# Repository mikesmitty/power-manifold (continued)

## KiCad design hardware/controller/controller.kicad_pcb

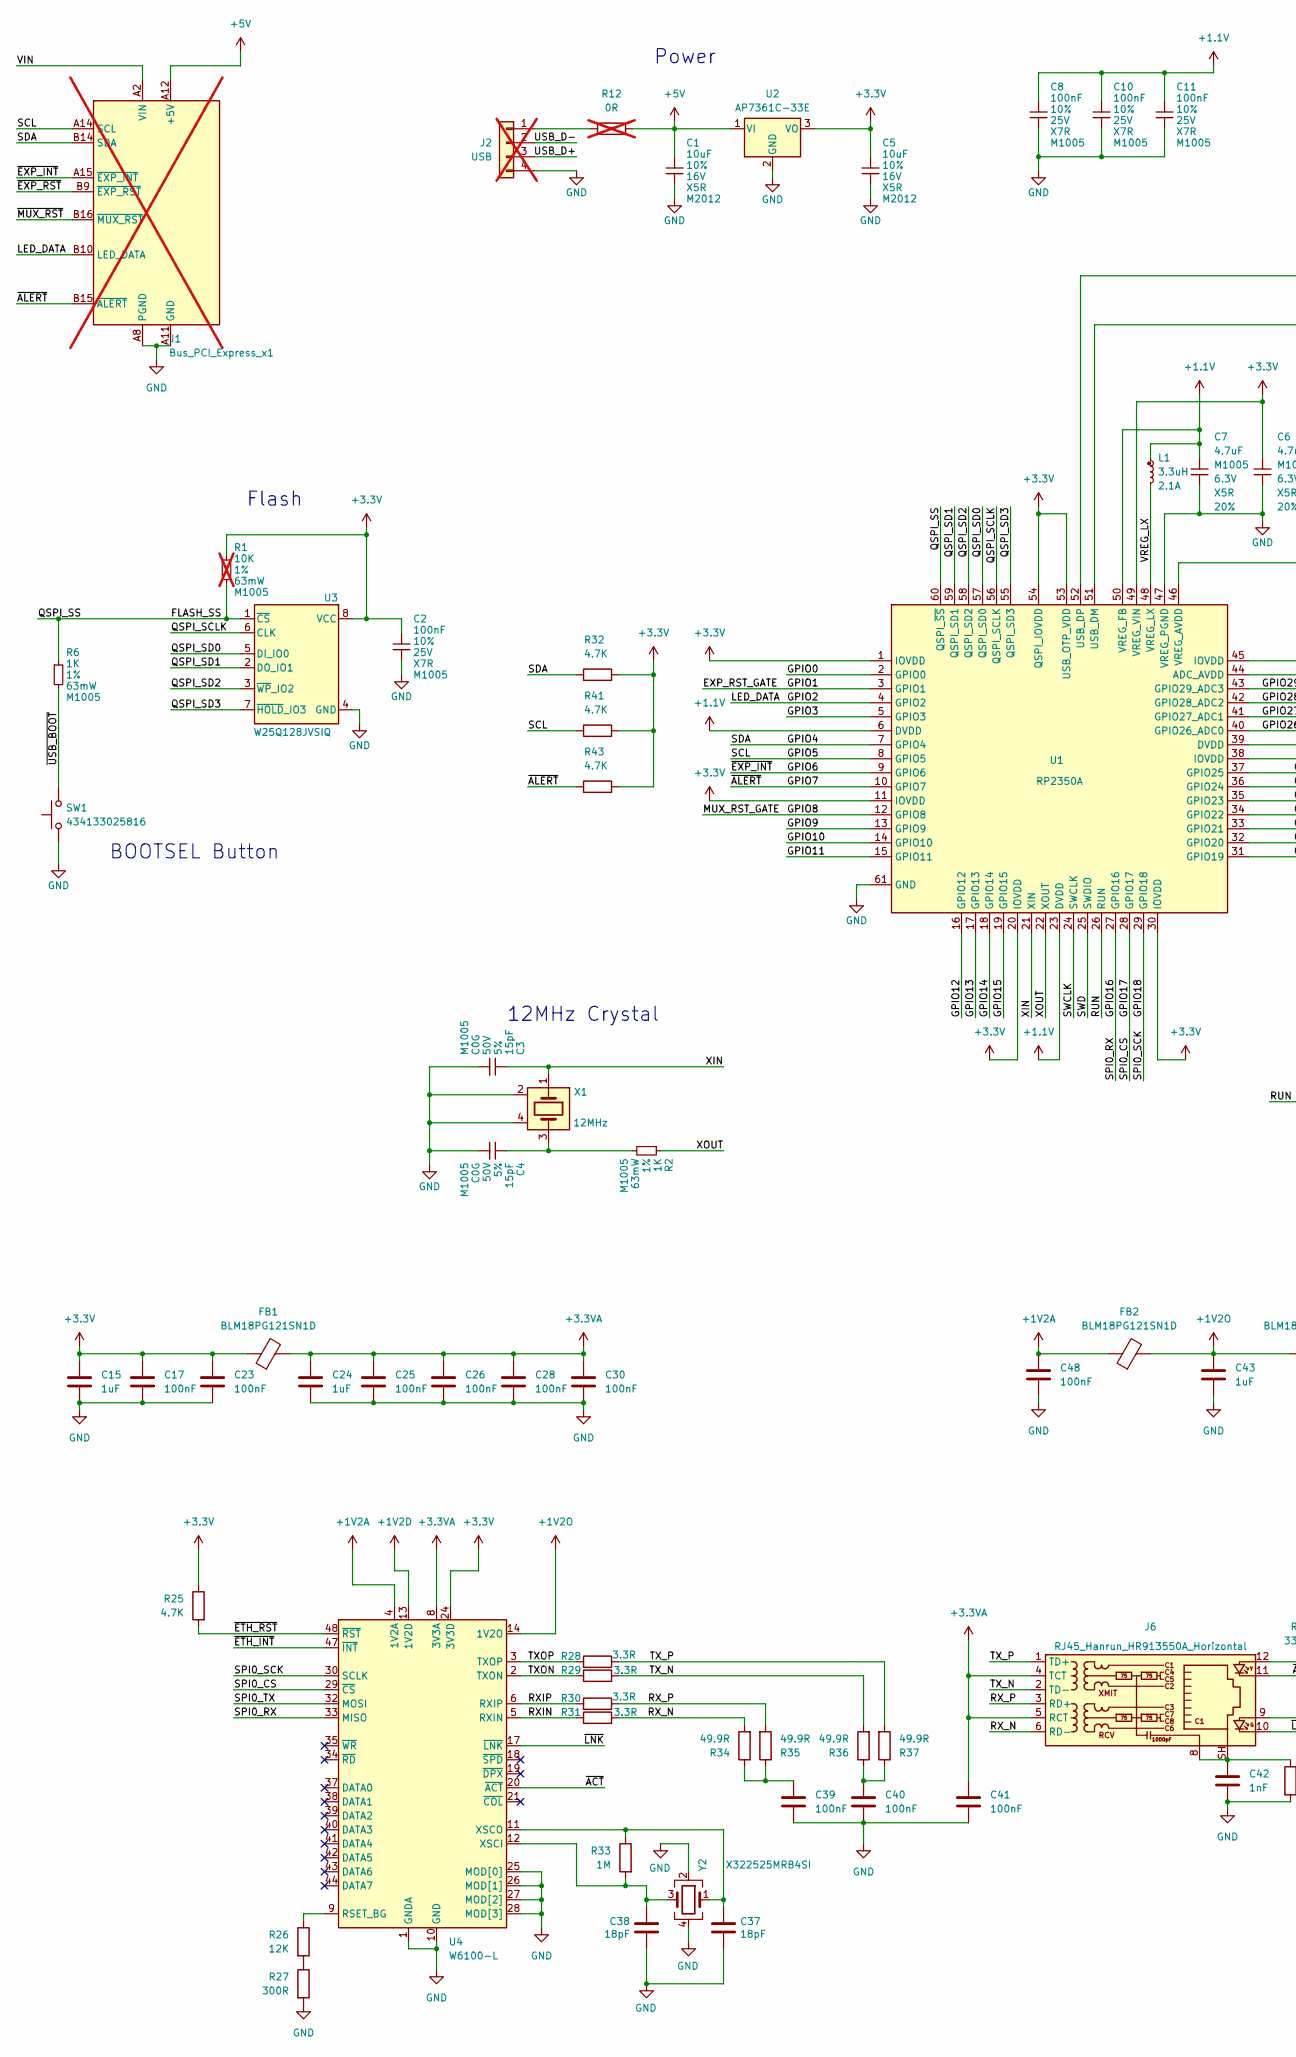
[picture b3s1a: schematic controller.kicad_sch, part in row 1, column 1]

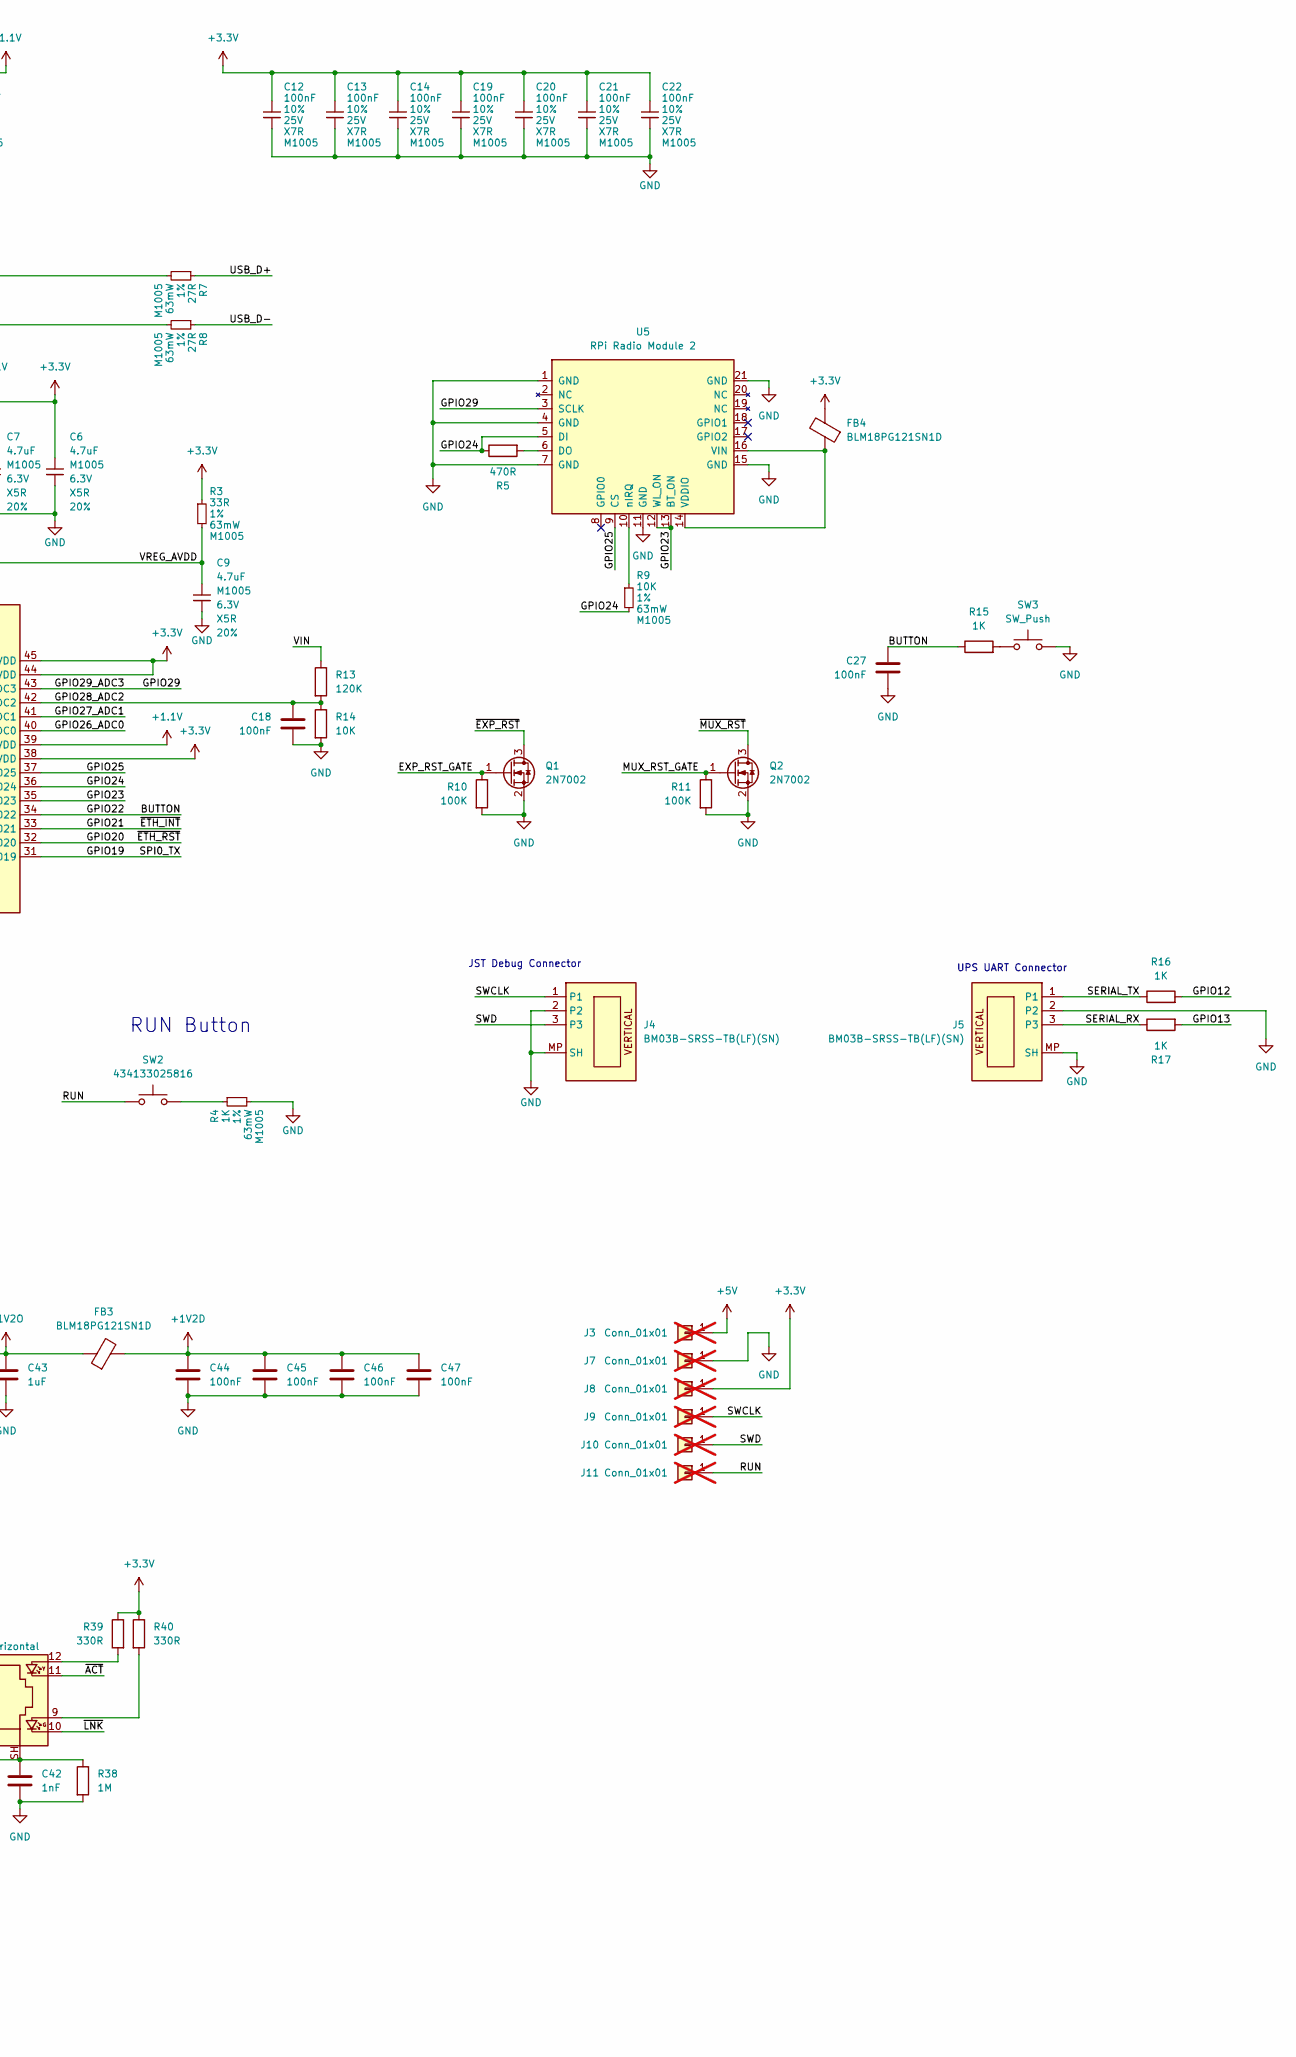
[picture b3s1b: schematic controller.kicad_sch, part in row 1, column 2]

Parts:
C1, C5: 10uF; C_0805_2012Metric; voltage 16V; tolerance 10%; part_uid RP-01GYSK-AVBE41; LCSC C1713
C2, C8, C10, C11, C12, C13, C14, C19, C20, C21, C22: 100nF; C_0402_1005Metric; voltage 25V; tolerance 10%; part_uid RP-01BJ9Y-KRGF41; LCSC C307331
C3, C4: 15pF; C_0402_1005Metric; voltage 50V; tolerance 5%; part_uid RP-01C89W-LLY9XV; LCSC C1548
C6, C7: 4.7uF; C_0402_Wide; voltage 6.3V; tolerance 20%; part_uid RP-019A1P-0C2GHY; LCSC C23733
C9: 4.7uF; C_0402_1005Metric; voltage 6.3V; tolerance 20%; part_uid RP-019A1P-0C2GHY; LCSC C23733
C15, C24, C43: 1uF; C_0402_1005Metric; LCSC C52923
C17, C18, C23, C25, C26, C27, C28, C30, C39, C40, C41, C44, C45, C46, C47, C48: 100nF; C_0402_1005Metric; LCSC C307331
C37, C38: 18pF; C_0402_1005Metric; LCSC C1549
C42: 1nF; C_1206_3216Metric; LCSC C9196
FB1, FB2, FB3, FB4: BLM18PG121SN1D; L_0603_1608Metric; LCSC C14709
J1: Bus_PCI_Express_x1; BUS_PCIexpress_x1; not fitted
J2: USB; PinHeader_1x04_P2.54mm_Vertical; not fitted
J3, J7, J8, J9, J10, J11: Conn_01x01; TestPoint_Pad_D1.5mm; not fitted
J4, J5: BM03B-SRSS-TB(LF)(SN); JST_SH_BM03B-SRSS-TB_1x03-1MP_P1.00mm_Vertical; manufacturer_pn BM03B-SRSS-TB(LF)(SN); LCSC C160389
J6: RJ45_Hanrun_HR913550A_Horizontal; RJ45_Hanrun_HR911105A_Horizontal; LCSC C163507
L1: 3.3uH; L_pol_2016; tolerance 20%; part_uid RP-01GY5D-2VC7WP; LCSC C42411119
Q1, Q2: 2N7002; SOT-23; LCSC C8545
R1: 10K; R_0402_1005Metric; tolerance 1%; voltage 50V; part_uid RP-019A1P-53DHSX; not fitted
R2, R4, R6: 1K; R_0402_1005Metric; tolerance 1%; voltage 50V; part_uid RP-019A1P-4Z6ZWY; LCSC C11702
R3: 33R; R_0402_1005Metric; tolerance 1%; voltage 50V; part_uid RP-019A1P-58PW9L; LCSC C25105
R5: 470R; R_0402_1005Metric; LCSC C25117
R7, R8: 27R; R_0402_1005Metric; tolerance 1%; voltage 50V; part_uid RP-01C89V-LTEYC4; LCSC C25100
R9: 10K; R_0402_1005Metric; tolerance 1%; voltage 50V; part_uid RP-019A1P-53DHSX; LCSC C25744
R10, R11: 100K; R_0402_1005Metric; LCSC C25741
R12: 0R; R_0603_1608Metric; not fitted
R13: 120K; R_0603_1608Metric; LCSC C25808
R14: 10K; R_0402_1005Metric; LCSC C25744
R15, R16, R17: 1K; R_0402_1005Metric; LCSC C11702
R25, R32, R41, R43: 4.7K; R_0402_1005Metric; LCSC C25900
R26: 12K; R_0402_1005Metric; Tolerance 1%; LCSC C25752
R27: 300R; R_0402_1005Metric; LCSC C25102
R28, R29, R30, R31: 3.3R; R_0402_1005Metric; LCSC C2933094
R33: 1M; R_0402_1005Metric; LCSC C26083
R34, R35, R36, R37: 49.9R; R_0402_1005Metric; LCSC C25120
R38: 1M; R_1206_3216Metric; LCSC C17927
R39, R40: 330R; R_0402_1005Metric; LCSC C25104
SW1, SW2: 434133025816; SW_Push_1P1T_NO_Vertical_Wuerth_434133025816; part_uid RP-01H0MT-6E9H8F; LCSC C5504987
SW3: SW_Push; SW_SPST_B3U-3000P; LCSC C963349
U1: RP2350A; QFN-60-1EP_7x7mm_P0.4mm_EP3.4x3.4mm_ThermalVias; part_uid RP-01HA9H-9K5E8T; LCSC C42411118
U2: AP7361C-33E; SOT-223-3_TabPin2; LCSC C500795
U3: W25Q128JVSIQ; SOIC-8_5.3x5.3mm_P1.27mm; voltage 2.7-3.6V; part_uid RP-01JWD4-F1H4N9; LCSC C97521
U4: W6100-L; LQFP-48_7x7mm_P0.5mm; LCSC C911393
U5: RPi Radio Module 2; RMC20452T; LCSC C49451547
X1: 12MHz; Crystal_SMD_Abracon_ABM8AIG-4Pin_3.2x2.5mm; tolerance 30ppm; part_uid RP-01G8X7-GS352B; LCSC C20625731
Y2: X322525MRB4SI; Crystal_SMD_3225-4Pin_3.2x2.5mm; LCSC C70593

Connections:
+1.1V: C7.1, C8.1, C10.1, C11.1, L1.1, U1.6 (DVDD), U1.23 (DVDD), U1.39 (DVDD), U1.50 (VREG_FB)
+1V2A: C48.1, FB2.1, U4.4 (1V2A)
+1V2D: C44.1, C45.1, C46.1, C47.1, FB3.2, U4.13 (1V2D), U4.22 (1V2D), U4.31 (1V2D), U4.45 (1V2D)
+1V2O: C43.1, FB2.2, FB3.1, U4.14 (1V2O)
+3.3V: C2.1, C5.1, C6.1, C12.1, C13.1, C14.1, C15.1, C17.1, C19.1, C20.1, C21.1, C22.1, C23.1, FB1.1, FB4.2, J8.1 (Pin_1_1), R1.1, R3.1, R25.1, R32.2, R39.1, R40.1, R41.2, R43.2, U1.1 (IOVDD), U1.11 (IOVDD), U1.20 (IOVDD), U1.30 (IOVDD), U1.38 (IOVDD), U1.44 (ADC_AVDD), U1.45 (IOVDD), U1.49 (VREG_VIN), U1.53 (USB_OTP_VDD), U1.54 (QSPI_IOVDD), U2.3 (VO), U3.8 (VCC), U4.24 (3V3D), U4.36 (3V3D)
+3.3VA: C24.1, C25.1, C26.1, C28.1, C30.1, C41.1, FB1.2, J6.4 (TCT), J6.5 (RCT), U4.8 (3V3A), U4.15 (3V3A)
+5V: C1.1, J1.A12 (+5V), J1.B12 (+5V), J3.1 (Pin_1_1), R12.2, U2.1 (VI)
/BUTTON: C27.1, R15.1, U1.34 (GPIO22)
/EXP_RST_GATE: Q1.1 (G), R10.1, U1.3 (GPIO1)
/FLASH_SS: R1.2, R6.1, U1.60 (QSPI_~SS), U3.1 (~CS)
/GPIO0: U1.2 (GPIO0)
/GPIO2: J1.B10 (LED_DATA), U1.4 (GPIO2)
/GPIO3: U1.5 (GPIO3)
/GPIO4: J1.B14 (SDA), R32.1, U1.7 (GPIO4)
/GPIO5: J1.A14 (SCL), R41.1, U1.8 (GPIO5)
/GPIO6: J1.A15 (~EXP_INT), U1.9 (GPIO6)
/GPIO7: J1.B15 (~ALERT), R43.1, U1.10 (GPIO7)
/GPIO8: Q2.1 (G), R11.1, U1.12 (GPIO8)
/GPIO9: U1.13 (GPIO9)
/GPIO10: U1.14 (GPIO10)
/GPIO11: U1.15 (GPIO11)
/GPIO12: R16.2, U1.16 (GPIO12)
/GPIO13: R17.2, U1.17 (GPIO13)
/GPIO14: U1.18 (GPIO14)
/GPIO15: U1.19 (GPIO15)
/GPIO16: U1.27 (GPIO16), U4.33 (MISO)
/GPIO17: U1.28 (GPIO17), U4.29 (~CS)
/GPIO18: U1.29 (GPIO18), U4.30 (SCLK)
/GPIO19: U1.31 (GPIO19), U4.32 (MOSI)
/GPIO20: R25.2, U1.32 (GPIO20), U4.48 (~RST)
/GPIO21: U1.33 (GPIO21), U4.47 (~INT)
/GPIO23: U1.35 (GPIO23), U5.12 (WL_ON), U5.13 (BT_ON)
/GPIO24: R5.1, R9.2, U1.36 (GPIO24), U5.5 (DI)
/GPIO25: U1.37 (GPIO25), U5.9 (CS)
/GPIO26_ADC0: U1.40 (GPIO26_ADC0)
/GPIO27_ADC1: U1.41 (GPIO27_ADC1)
/GPIO28_ADC2: C18.1, R13.2, R14.1, U1.42 (GPIO28_ADC2)
/GPIO29: U1.43 (GPIO29_ADC3), U5.3 (SCLK)
/QSPI_SCLK: U1.56 (QSPI_SCLK), U3.6 (CLK)
/QSPI_SD0: U1.57 (QSPI_SD0), U3.5 (DI_IO0)
/QSPI_SD1: U1.59 (QSPI_SD1), U3.2 (DO_IO1)
/QSPI_SD2: U1.58 (QSPI_SD2), U3.3 (~WP_IO2)
/QSPI_SD3: U1.55 (QSPI_SD3), U3.7 (~HOLD_IO3)
/RUN: J11.1 (Pin_1_1), SW2.2, U1.26 (RUN)
/RXIN: R31.1, U4.5 (RXIN)
/RXIP: R30.1, U4.6 (RXIP)
/RX_N: J6.6 (RD-), R31.2, R34.2
/RX_P: J6.3 (RD+), R30.2, R35.2
/SERIAL_RX: J5.3, R17.1
/SERIAL_TX: J5.1, R16.1
/SWCLK: J4.1, J9.1 (Pin_1_1), U1.24 (SWCLK)
/SWD: J4.3, J10.1 (Pin_1_1), U1.25 (SWDIO)
/TXON: R29.1, U4.2 (TXON)
/TXOP: R28.1, U4.3 (TXOP)
/TX_N: J6.2 (TD-), R29.2, R36.2
/TX_P: J6.1 (TD+), R28.2, R37.2
/USB_D+: J2.3, R7.1
/USB_D-: J2.2, R8.1
/VIN: J1.A2 (VIN), J1.A3 (VIN), J1.A4 (VIN), J1.A5 (VIN), J1.A6 (VIN), J1.A7 (VIN), R13.1
/VREG_AVDD: C9.1, R3.2, U1.46 (VREG_AVDD)
/VREG_LX: L1.2, U1.48 (VREG_LX)
/XIN: C3.1, U1.21 (XIN), X1.1
/XOUT: R2.1, U1.22 (XOUT)
/~ACT: J6.11, U4.20 (~ACT)
/~EXP_RST: J1.B9 (~EXP_RST), Q1.3 (D)
/~LNK: J6.10, U4.17 (~LNK)
/~MUX_RST: J1.B16 (~MUX_RST), Q2.3 (D)
/~USB_BOOT: R6.2, SW1.2
GND: C1.2, C2.2, C3.2, C4.2, C5.2, C6.2, C7.2, C8.2, C9.2, C10.2, C11.2, C12.2, C13.2, C14.2, C15.2, C17.2, C18.2, C19.2, C20.2, C21.2, C22.2, C23.2, C24.2, C25.2, C26.2, C27.2, C28.2, C30.2, C37.2, C38.2, C39.2, C40.2, C41.2, C42.2, C43.2, C44.2, C45.2, C46.2, C47.2, C48.2, J1.A1 (GND), J1.A8 (PGND), J1.A9 (PGND), J1.A10 (PGND), J1.A11 (GND), J1.A13 (GND), J1.A16 (GND), J1.A17 (GND), J1.A18 (GND), J1.B1 (PGND), J1.B2 (PGND), J1.B3 (PGND), J1.B4 (PGND), J1.B5 (PGND), J1.B6 (PGND), J1.B7 (PGND), J1.B8 (PGND), J1.B11 (GND), J1.B13 (GND), J1.B17 (GND), J1.B18 (GND), J2.4, J4.2, J4.MP (SH), J5.2, J5.MP (SH), J7.1 (Pin_1_1), Q1.2 (S), Q2.2 (S), R4.2, R10.2, R11.2, R14.2, R27.2, R38.2, SW1.1, SW3.2, U1.47 (VREG_PGND), U1.61 (GND), U2.2 (GND), U3.4 (GND), U4.1 (GNDA), U4.7 (GNDA), U4.10 (GND), U4.16 (GNDA), U4.23 (GND), U4.25 (MOD[0]), U4.26 (MOD[1]), U4.27 (MOD[2]), U4.28 (MOD[3]), U4.46 (GND), U5.1 (GND), U5.4 (GND), U5.7 (GND), U5.11 (GND), U5.15 (GND), U5.21 (GND), X1.2, X1.4, Y2.2, Y2.4
unnamed: C4.1, R2.2, X1.3
unnamed: C39.1, R34.1, R35.1
unnamed: C40.1, R36.1, R37.1
unnamed: C42.1, J6.8, J6.SH, R38.1
unnamed: J2.1, R12.1
unnamed: J6.9, R40.2
unnamed: J6.12, R39.2
unnamed: R4.1, SW2.1
unnamed: R15.2, SW3.1
unnamed: R26.2, R27.1
unnamed: R8.2, U1.51 (USB_DM)
unnamed: R7.2, U1.52 (USB_DP)
unnamed: R26.1, U4.9 (RSET_BG)
unnamed: C38.1, R33.2, U4.12 (XSCI), Y2.3
unnamed: C37.1, R33.1, U4.11 (XSCO), Y2.1
unnamed: R5.2, U5.6 (DO)
unnamed: FB4.1, U5.14 (VDDIO), U5.16 (VIN)
unnamed: R9.1, U5.10 (nIRQ)

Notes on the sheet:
12MHz Crystal
RUN Button
Flash
BOOTSEL Button
JST Debug Connector
UPS UART Connector
Power

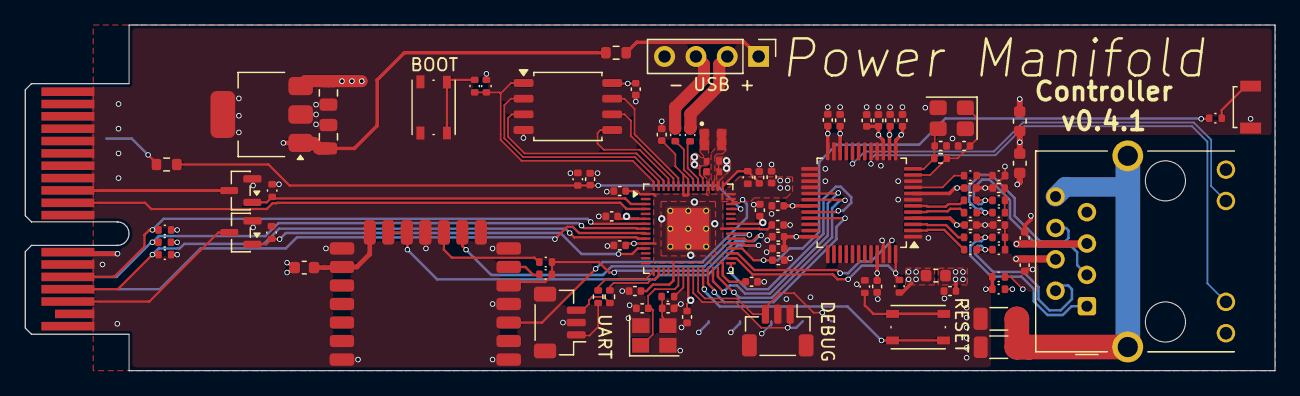
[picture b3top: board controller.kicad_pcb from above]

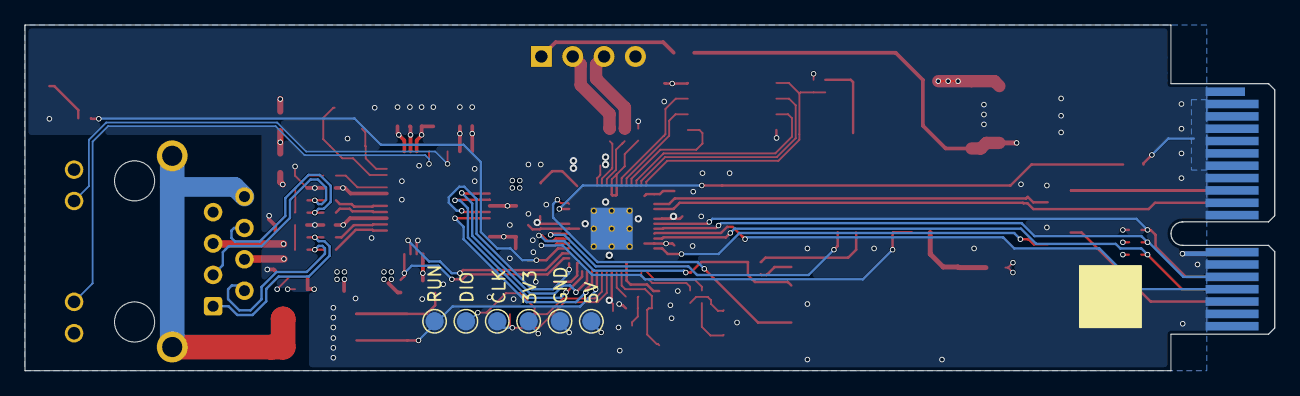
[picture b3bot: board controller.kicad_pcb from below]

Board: 4 copper layers, 101.2 x 28.0 mm, 103 parts (6 on the bottom side), 78 nets.

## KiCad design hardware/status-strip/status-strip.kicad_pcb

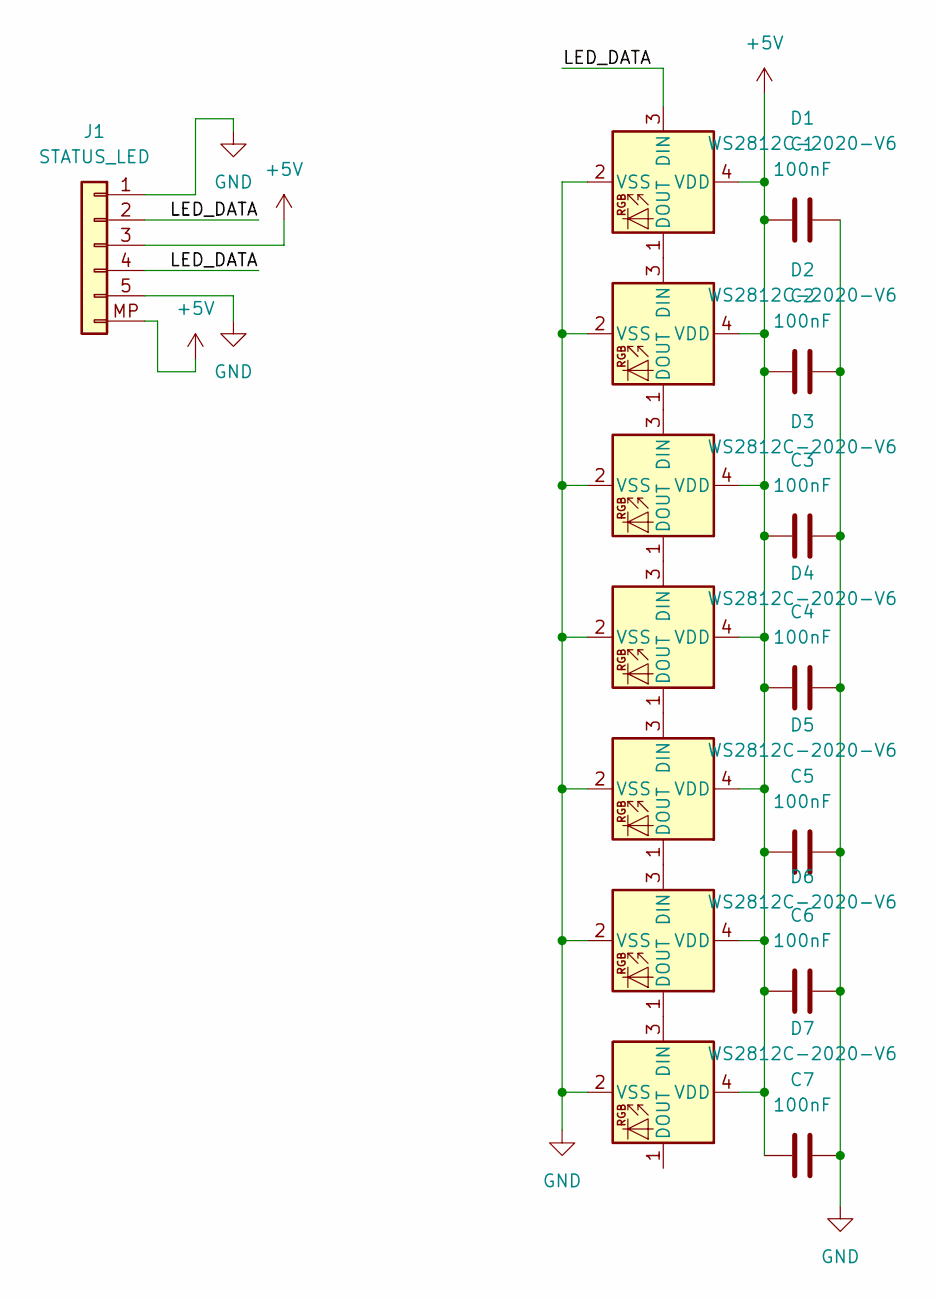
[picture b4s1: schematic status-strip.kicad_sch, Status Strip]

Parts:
C1, C2, C3, C4, C5, C6, C7: 100nF; C_0402_1005Metric; LCSC C307331
D1, D2, D3, D4, D5, D6, D7: WS2812C-2020-V6; LED_WS2812B-2020_PLCC4_2.0x2.0mm; LCSC C55109522
J1: STATUS_LED; JST_SH_BM05B-SRSS-TB_1x05-1MP_P1.00mm_Vertical; LCSC C160391

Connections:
+5V: C1.1, C2.1, C3.1, C4.1, C5.1, C6.1, C7.1, D1.4 (VDD), D2.4 (VDD), D3.4 (VDD), D4.4 (VDD), D5.4 (VDD), D6.4 (VDD), D7.4 (VDD), J1.3, J1.MP (Pin_6)
/LED_DATA: D1.3 (DIN), J1.2, J1.4
GND: C1.2, C2.2, C3.2, C4.2, C5.2, C6.2, C7.2, D1.2 (VSS), D2.2 (VSS), D3.2 (VSS), D4.2 (VSS), D5.2 (VSS), D6.2 (VSS), D7.2 (VSS), J1.1, J1.5
unnamed: D1.1 (DOUT), D2.3 (DIN)
unnamed: D2.1 (DOUT), D3.3 (DIN)
unnamed: D3.1 (DOUT), D4.3 (DIN)
unnamed: D4.1 (DOUT), D5.3 (DIN)
unnamed: D5.1 (DOUT), D6.3 (DIN)
unnamed: D6.1 (DOUT), D7.3 (DIN)

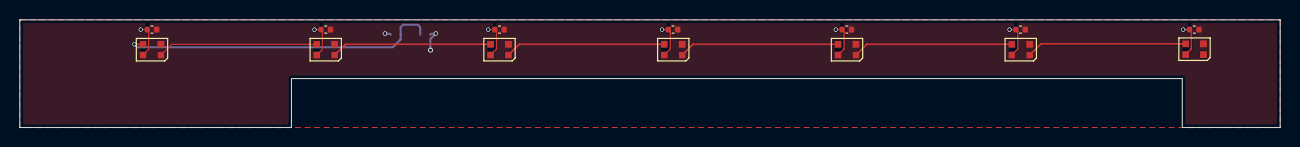
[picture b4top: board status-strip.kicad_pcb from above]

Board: 2 copper layers, 128.8 x 11.0 mm, 15 parts (1 on the bottom side), 9 nets.

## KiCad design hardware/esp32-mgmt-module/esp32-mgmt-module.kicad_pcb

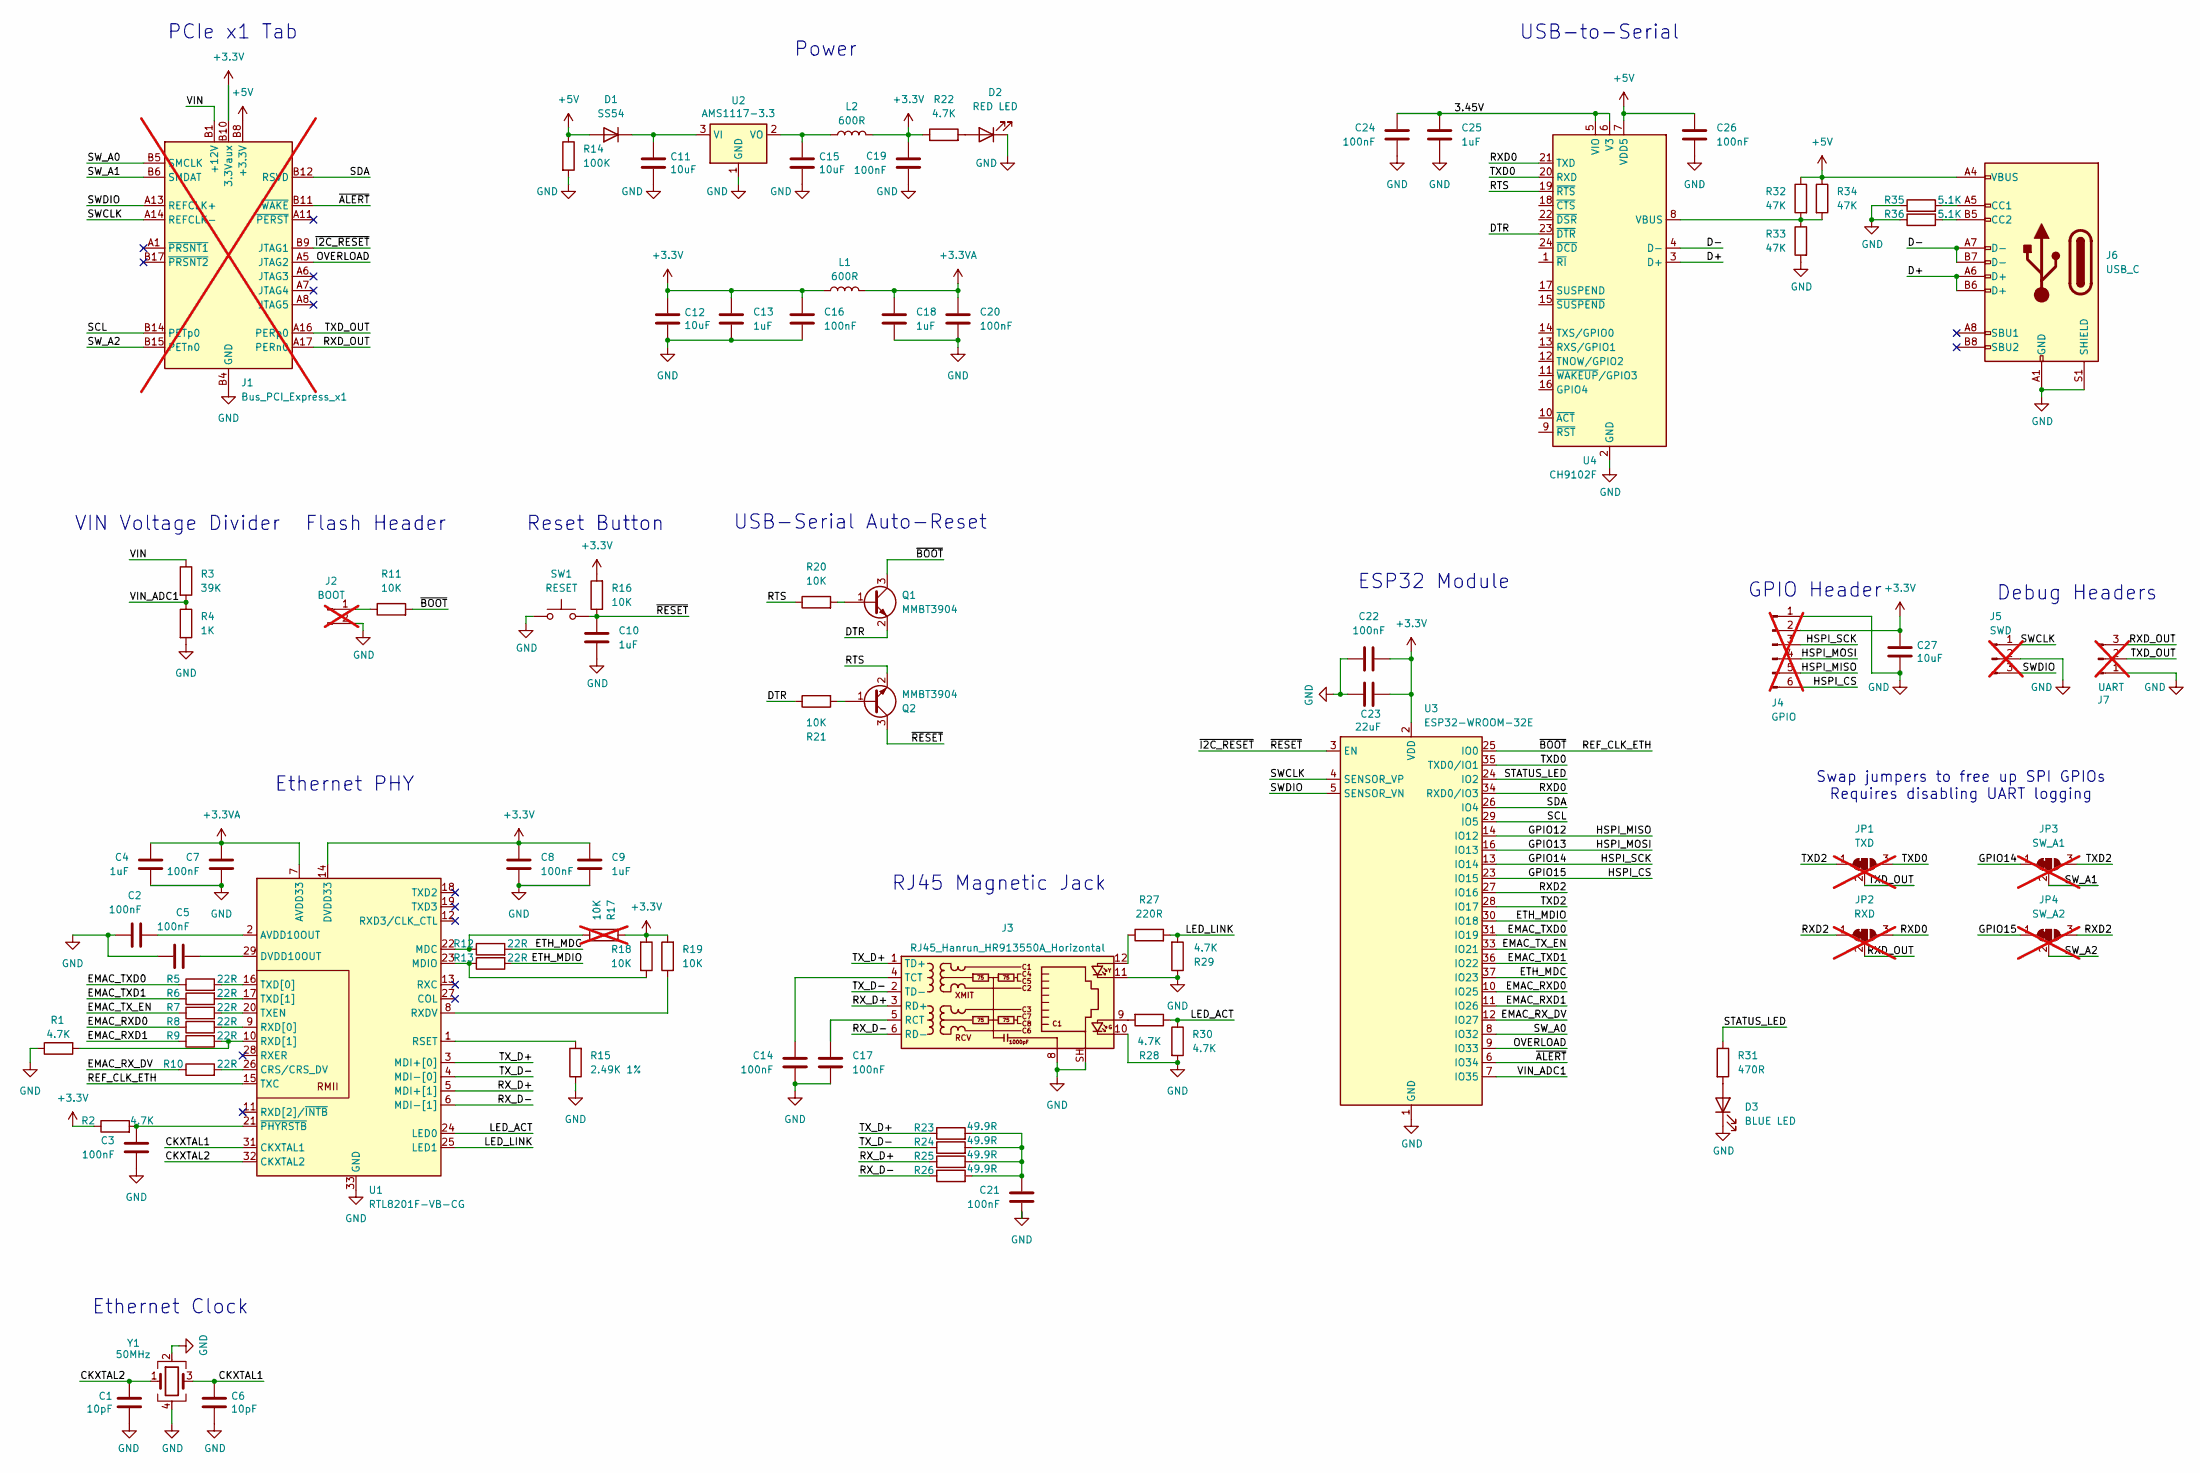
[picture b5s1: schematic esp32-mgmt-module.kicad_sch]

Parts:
C1, C6: 10pF; C_0402_1005Metric; LCSC C32949
C2, C3, C5, C7, C8, C14, C16, C17, C19, C20, C21, C22, C24, C26: 100nF; C_0402_1005Metric; LCSC C1525
C4, C9, C10, C13, C18, C25: 1uF; C_0402_1005Metric; LCSC C52923
C11, C12, C15, C27: 10uF; C_0402_1005Metric; LCSC C15525
C23: 22uF; C_0603_1608Metric; LCSC C59461
D1: SS54; D_SMA; LCSC C22452
D2: RED LED; LED_0603_1608Metric; LCSC C2286
D3: BLUE LED; LED_0603_1608Metric; LCSC C965807
J1: Bus_PCI_Express_x1; BUS_PCIexpress_x1; not fitted
J2: BOOT; PinHeader_1x02_P2.54mm_Vertical; not fitted
J3: RJ45_Hanrun_HR913550A_Horizontal; RJ45_Hanrun_HR911105A_Horizontal; LCSC C163507
J4: GPIO; PinHeader_1x06_P2.54mm_Vertical; not fitted
J5: SWD; PinHeader_1x03_P2.54mm_Vertical; not fitted
J6: USB_C; USB_C_Receptacle_XKB_U262-16XN-4BVC11; LCSC C393939
J7: UART; PinHeader_1x03_P2.54mm_Vertical; not fitted
JP1: TXD; SolderJumper-3_P1.3mm_Bridged12_RoundedPad1.0x1.5mm; not fitted
JP2: RXD; SolderJumper-3_P1.3mm_Bridged12_RoundedPad1.0x1.5mm; not fitted
JP3: SW_A1; SolderJumper-3_P1.3mm_Bridged12_RoundedPad1.0x1.5mm; not fitted
JP4: SW_A2; SolderJumper-3_P1.3mm_Bridged12_RoundedPad1.0x1.5mm; not fitted
L1, L2: 600R; L_0603_1608Metric; LCSC C97000
Q1, Q2: MMBT3904; SOT-23; LCSC C20526
R1, R2, R22, R28, R29, R30: 4.7K; R_0402_1005Metric; LCSC C25900
R3: 39K; R_0402_1005Metric; LCSC C25783
R4: 1K; R_0402_1005Metric; LCSC C11702
R5, R6, R7, R8, R9, R10, R12, R13: 22R; R_0402_1005Metric; LCSC C25092
R11, R16, R18, R19, R20, R21: 10K; R_0402_1005Metric; LCSC C25744
R14: 100K; R_0402_1005Metric; LCSC C25741
R15: 2.49K 1%; R_0402_1005Metric; LCSC C25884
R17: 10K; R_0402_1005Metric; LCSC C25744; not fitted
R23, R24, R25, R26: 49.9R; R_0402_1005Metric; LCSC C25120
R27: 220R; R_0402_1005Metric; LCSC C25091
R31: 470R; R_0402_1005Metric; LCSC C25117
R32, R33, R34: 47K; R_0402_1005Metric; LCSC C25792
R35, R36: 5.1K; R_0402_1005Metric; LCSC C25905
SW1: RESET; Yuandi_TS-1037-Ax; LCSC C499328
U1: RTL8201F-VB-CG; QFN-32-1EP_5x5mm_P0.5mm_EP3.6x3.6mm_ThermalVias; LCSC C45044
U2: AMS1117-3.3; SOT-223-3_TabPin2; LCSC C6186
U3: ESP32-WROOM-32E; LCSC C701341
U4: CH9102F; QFN-24-1EP_4x4mm_P0.5mm_EP2.6x2.6mm; LCSC C2858418
Y1: 50MHz; Crystal_SMD_3225-4Pin_3.2x2.5mm; LCSC C2682781

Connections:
+3.3V: C8.1, C9.1, C12.1, C13.1, C16.1, C19.1, C22.2, C23.2, C27.1, J1.B10 (3.3Vaux), J4.2, L1.1, L2.2, R2.1, R16.2, R17.2, R18.2, R19.2, R22.1, U1.14 (DVDD33), U3.2 (VDD)
+3.3VA: C4.1, C7.1, C18.1, C20.1, L1.2, U1.7 (AVDD33), U1.30 (AVDD33)
+5V: C26.1, D1.2 (A), J1.A9 (+3.3V), J1.A10 (+3.3V), J1.B8 (+3.3V), J6.A4 (VBUS), J6.A9 (VBUS), J6.B4 (VBUS), J6.B9 (VBUS), R14.1, R32.1, R34.1, U4.7 (VDD5)
/3.45V: C24.1, C25.1, U4.5 (VIO), U4.6 (V3)
/CKXTAL1: C6.1, U1.31 (CKXTAL1), Y1.3
/CKXTAL2: C1.1, U1.32 (CKXTAL2), Y1.1
/D+: J6.A6 (D+), J6.B6 (D+), U4.3 (D+)
/D-: J6.A7 (D-), J6.B7 (D-), U4.4 (D-)
/DTR: Q1.2 (E), R21.1, U4.23 (~DTR)
/EMAC_RXD0: R8.1, U3.10 (IO25)
/EMAC_RXD1: R9.1, U3.11 (IO26)
/EMAC_RX_DV: R10.1, U3.12 (IO27)
/EMAC_TXD0: R5.1, U3.31 (IO19)
/EMAC_TXD1: R6.1, U3.36 (IO22)
/EMAC_TX_EN: R7.1, U3.33 (IO21)
/ETH_MDC: R12.2, U3.37 (IO23)
/ETH_MDIO: R13.2, U3.30 (IO18)
/GPIO12: J4.5, U3.14 (IO12)
/GPIO13: J4.4, U3.16 (IO13)
/GPIO14: J4.3, JP3.1 (A), U3.13 (IO14)
/GPIO15: J4.6, JP4.1 (A), U3.23 (IO15)
/LED_ACT: R28.1, R30.1, U1.24 (LED0)
/LED_LINK: R27.2, R29.2, U1.25 (LED1)
/OVERLOAD: J1.A5 (JTAG2), U3.9 (IO33)
/REF_CLK_ETH: Q1.3 (C), R11.2, U1.15 (TXC), U3.25 (IO0)
/RTS: Q2.2 (E), R20.1, U4.19 (~RTS)
/RXD0: JP2.3 (B), U3.34 (RXD0/IO3), U4.21 (TXD)
/RXD2: JP2.1 (A), JP4.3 (B), U3.27 (IO16)
/RXD_OUT: J1.A17 (PERn0), J7.3, JP2.2 (C)
/RX_D+: J3.3 (RD+), R25.1, U1.5 (MDI+[1])
/RX_D-: J3.6 (RD-), R26.1, U1.6 (MDI-[1])
/SCL: J1.B14 (PETp0), U3.29 (IO5)
/SDA: J1.B12 (RSVD), U3.26 (IO4)
/STATUS_LED: R31.1, U3.24 (IO2)
/SWCLK: J1.A14 (REFCLK-), J5.1, U3.4 (SENSOR_VP)
/SWDIO: J1.A13 (REFCLK+), J5.3, U3.5 (SENSOR_VN)
/SW_A0: J1.B5 (SMCLK), U3.8 (IO32)
/SW_A1: J1.B6 (SMDAT), JP3.2 (C)
/SW_A2: J1.B15 (PETn0), JP4.2 (C)
/TXD0: JP1.3 (B), U3.35 (TXD0/IO1), U4.20 (RXD)
/TXD2: JP1.1 (A), JP3.3 (B), U3.28 (IO17)
/TXD_OUT: J1.A16 (PERp0), J7.2, JP1.2 (C)
/TX_D+: J3.1 (TD+), R23.1, U1.3 (MDI+[0])
/TX_D-: J3.2 (TD-), R24.1, U1.4 (MDI-[0])
/VIN: J1.A2 (+12V), J1.A3 (+12V), J1.B1 (+12V), J1.B2 (+12V), J1.B3 (+12V), R3.1
/VIN_ADC1: R3.2, R4.1, U3.7 (IO35)
/~ALERT: J1.B11 (~WAKE), U3.6 (IO34)
/~I2C_RESET: C10.1, J1.B9 (JTAG1), Q2.3 (C), R16.1, SW1.2, U3.3 (EN)
GND: C1.2, C2.1, C3.2, C4.2, C5.1, C6.2, C7.2, C8.2, C9.2, C10.2, C11.2, C12.2, C13.2, C14.2, C15.2, C16.2, C17.2, C18.2, C19.2, C20.2, C21.2, C22.1, C23.1, C24.2, C25.2, C26.2, C27.2, D2.1 (K), D3.1 (K), J1.A4 (GND), J1.A12 (GND), J1.A15 (GND), J1.A18 (GND), J1.B4 (GND), J1.B7 (GND), J1.B13 (GND), J1.B16 (GND), J1.B18 (GND), J2.2, J3.8, J3.10, J3.11, J3.SH, J4.1, J5.2, J6.A1 (GND), J6.A12 (GND), J6.B1 (GND), J6.B12 (GND), J6.S1 (SHIELD), J7.1, R1.1, R4.2, R14.2, R15.1, R29.1, R30.2, R33.2, R35.1, R36.1, SW1.1, U1.33 (GND), U2.1 (GND), U3.1 (GND), U3.15 (GND), U3.38 (GND), U3.39 (GND), U4.2 (GND), U4.25 (GND), Y1.2, Y1.4
unnamed: C21.1, R23.2, R24.2, R25.2, R26.2
unnamed: C11.1, D1.1 (K), U2.3 (VI)
unnamed: D2.2 (A), R22.2
unnamed: D3.2 (A), R31.2
unnamed: J2.1, R11.1
unnamed: J3.9, R28.2
unnamed: J3.12, R27.1
unnamed: C17.1, J3.5 (RCT)
unnamed: C14.1, J3.4 (TCT)
unnamed: J6.A5 (CC1), R35.2
unnamed: J6.B5 (CC2), R36.2
unnamed: Q1.1 (B), R20.2
unnamed: Q2.1 (B), R21.2
unnamed: C2.2, U1.2 (AVDD10OUT)
unnamed: R10.2, U1.26 (CRS/CRS_DV)
unnamed: C5.2, U1.29 (DVDD10OUT)
unnamed: R12.1, R17.1, U1.22 (MDC)
unnamed: R13.1, R18.1, U1.23 (MDIO)
unnamed: R15.2, U1.1 (RSET)
unnamed: R19.1, U1.8 (RXDV)
unnamed: R8.2, U1.9 (RXD[0])
unnamed: R1.2, R9.2, U1.10 (RXD[1])
unnamed: R5.2, U1.16 (TXD[0])
unnamed: R6.2, U1.17 (TXD[1])
unnamed: R7.2, U1.20 (TXEN)
unnamed: C3.1, R2.2, U1.21 (~PHYRSTB)
unnamed: C15.1, L2.1, U2.2 (VO)
unnamed: R32.2, R33.1, R34.2, U4.8 (VBUS)

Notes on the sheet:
Ethernet Clock
Reset Button
GPIO Header
Flash Header
Swap jumpers to free up SPI GPIOs Requires disabling UART logging
USB-to-Serial
VIN Voltage Divider
Power
Ethernet PHY
PCIe x1 Tab
RJ45 Magnetic Jack
USB-Serial Auto-Reset
ESP32 Module
Debug Headers

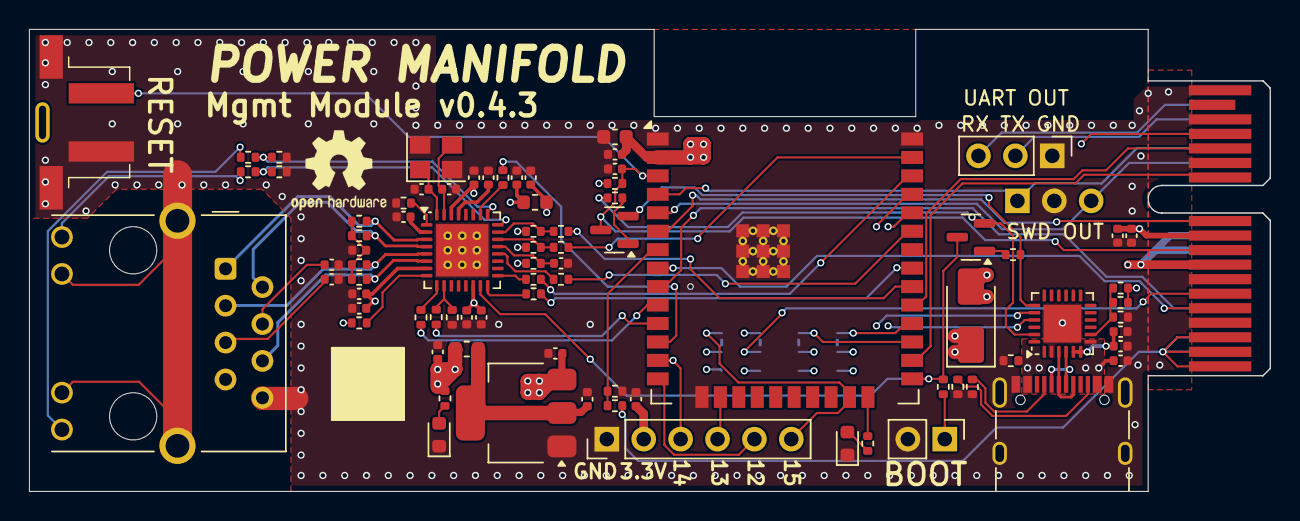
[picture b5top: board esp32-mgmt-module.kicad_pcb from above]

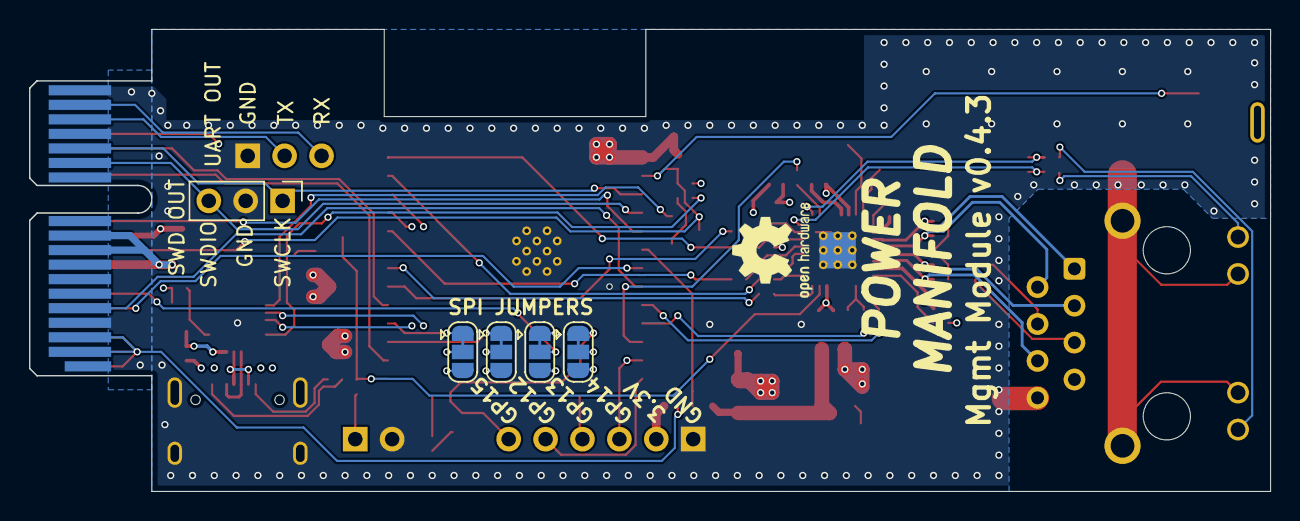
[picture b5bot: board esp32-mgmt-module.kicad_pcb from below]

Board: 4 copper layers, 85.4 x 31.8 mm, 87 parts (5 on the bottom side), 77 nets.
